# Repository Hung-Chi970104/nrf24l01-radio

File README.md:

# Custom 2.4 GHz Radio Module

**A custom nRF24L01 radio PCB with a printed antenna, demonstrated in a STEM-club RC car across an approximately 30 m indoor test area.**

[PCB layout](#pcb-layout) · [Schematic](radio.kicad_sch) · [Bring-up examples](#radio-bring-up) · [RC-car system](https://github.com/Hung-Chi970104/rukus)

## PCB layout

*Copper overview rendered from the original KiCad file. Front copper is red; back copper is blue; vias are green. Silkscreen and fabrication layers are omitted.*

## What I built

- Designed and built a custom nRF24L01 transceiver PCB with a **meandered inverted-F trace antenna based on TI AN043**.
- Integrated the RF matching network, **16 MHz crystal** and supply decoupling with the printed antenna.
- Integrated the radio with the custom Rukus controller and demonstrated reliable RC-car control across an **approximately 30 m indoor test area**.

The indoor result is an observed RC-car demonstration, not a measured packet-loss or maximum-range specification.

## Original 3D render

## Design

| Block | Implementation |
|---|---|
| Radio | nRF24L01 2.4 GHz transceiver |
| Host connection | SPI plus CE and CSN control |
| Reference clock | 16 MHz crystal |
| RF path | Matching network and printed meandered inverted-F antenna |
| Antenna reference | [Texas Instruments AN043](https://www.ti.com/lit/an/swra117d/swra117d.pdf) |
| System demonstration | [Rukus RC car and videos](https://github.com/Hung-Chi970104/rukus#working-hardware) |

The antenna follows TI's reference geometry; this project does not claim TI's reference-board RF measurements as measurements of this PCB.

## Radio bring-up

The [transmitter](examples/transmitter.py) sends numbered messages and reports whether an acknowledgment arrives. The [receiver](examples/receiver.py) prints the received messages. These are original MicroPython examples copied from Rukus.

1. Install MicroPython and a compatible `nrf24l01.py` driver on each host.
2. Check wiring against the [schematic](radio.kicad_sch) before powering the board.
3. The examples use SPI 0: SCK GP2, MOSI GP3, MISO GP4, CSN GP5 and CE GP6. Adapt these to the actual host wiring.
4. Start the receiver before the transmitter. Both examples use the five-byte address `Node1`.
5. Observe transmitted messages, acknowledgment status and received text in the serial consoles.

The driver is a separate dependency; it is not bundled here. The examples test the radio link and are not the complete RC-car application.

## Files

| File | Purpose |
|---|---|
| [radio.kicad_pro](radio.kicad_pro) | KiCad project |
| [radio.kicad_sch](radio.kicad_sch) | Circuit schematic |
| [radio.kicad_pcb](radio.kicad_pcb) | Routed PCB and antenna geometry |
| [radio.pcb3d](radio.pcb3d) | Original 3D project asset |
| [production/](production/) | Original manufacturing export and netlist |
| [examples/](examples/) | Transmit / receive bring-up examples |

## Origin

Extracted from [Hung-Chi970104/rukus — radio/](https://github.com/Hung-Chi970104/rukus/tree/7c238e4ea9ec795f958542f99792d99c4606db71/radio). The circuit, PCB, manufacturing exports and original render are copied unchanged. Existing Rukus links continue to work; historical backup archives remain in that repository.

Designed and built by Hung-Chi Wang.

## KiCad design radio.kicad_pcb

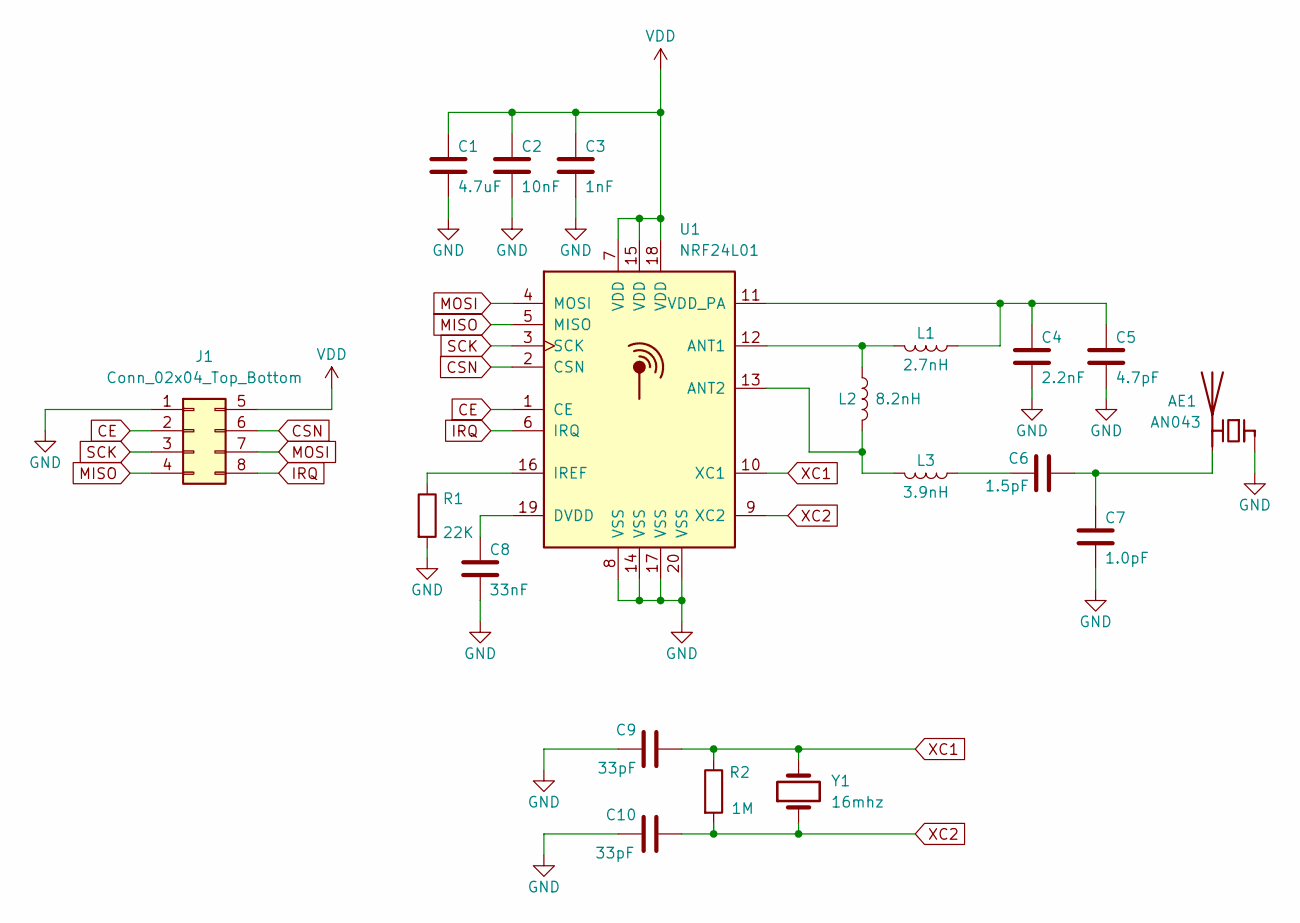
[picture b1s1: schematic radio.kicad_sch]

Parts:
AE1: AN043
C1: 4.7uF; C_0402_1005Metric
C2: 10nF; C_0402_1005Metric
C3: 1nF; C_0402_1005Metric
C4: 2.2nF; C_0402_1005Metric
C5: 4.7pF; C_0402_1005Metric
C6: 1.5pF; C_0402_1005Metric
C7: 1.0pF; C_0402_1005Metric
C8: 33nF; C_0402_1005Metric
C9, C10: 33pF; C_0402_1005Metric
J1: Conn_02x04_Top_Bottom; PinHeader_2x04_P2.54mm_Vertical
L1: 2.7nH; L_0402_1005Metric
L2: 8.2nH; L_0402_1005Metric
L3: 3.9nH; L_0402_1005Metric
R1: 22K; R_0402_1005Metric
R2: 1M; R_0402_1005Metric
U1: NRF24L01; QFN-20-1EP_4x4mm_P0.5mm_EP2.5x2.5mm
Y1: 16mhz; Crystal_HC49-4H_Vertical

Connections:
CE: J1.2, U1.1 (CE)
CSN: J1.6, U1.2 (CSN)
GND: AE1.1 (FEED), C1.2, C2.2, C3.2, C4.2, C5.2, C7.2, C8.2, C9.1, C10.1, J1.1, R1.2, U1.8 (VSS), U1.14 (VSS), U1.17 (VSS), U1.20 (VSS)
IRQ: J1.8, U1.6 (IRQ)
MISO: J1.4, U1.5 (MISO)
MOSI: J1.7, U1.4 (MOSI)
unnamed: AE1.2 (PCB_Trace), C6.2, C7.1
unnamed: C6.1, L3.1
unnamed: L1.2, L2.1, U1.12 (ANT1)
unnamed: L2.2, L3.2, U1.13 (ANT2)
unnamed: C8.1, U1.19 (DVDD)
unnamed: R1.1, U1.16 (IREF)
unnamed: C4.1, C5.1, L1.1, U1.11 (VDD_PA)
SCK: J1.3, U1.3 (SCK)
VDD: C1.1, C2.1, C3.1, J1.5, U1.7 (VDD), U1.15 (VDD), U1.18 (VDD)
XC1: C9.2, R2.1, U1.10 (XC1), Y1.2
XC2: C10.2, R2.2, U1.9 (XC2), Y1.1

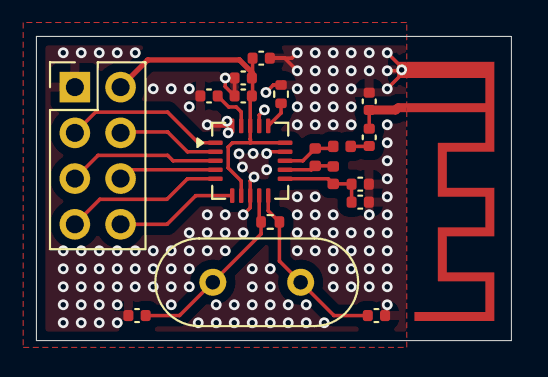
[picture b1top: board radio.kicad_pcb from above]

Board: 2 copper layers, 26.4 x 16.9 mm, 19 parts (0 on the bottom side), 17 nets.
